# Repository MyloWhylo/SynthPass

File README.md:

# SynthPass

An open-source protocol & hardware design for to detect nose boops & transfer simple data, designed for protogen/synth fursuits.

Built to solve a very important problem. With SynthPass, you won't have to break character or pull off your paws and fumble with your phone to trade contact details. Just nose-boop, and SynthPass will automagically trade a small chunk of user-defined data, like a web link, username, or anything else that can fit in a couple hundred bytes of plain text. Then plug in your SynthPass at the end of the day and download all the data you've collected.

SynthPass is also designed to easily interface with nearly any protogen/synth fursuit. SynthPass hardware can be powered by a single 3.3V supply, and supports digital several digital interface options.

## Features

- ### Simple interface to fursuits
	- GPIO: pin HIGH (3.3V) when booped, LOW (0V) when not booped. Additional pin that's high
	- UART: Message for boop start/end
	- I2C: Register for boop status
    - Don't want to modify your firmware or connect the digital pins to your controller? The GPIO output can also drive an LED to indicate when another SynthPass is nearby and when a nose boop is detected.
- ### Advanced interface
	- UART/I2C Only
	- Approximate range & unique ID of peer prior to boop
	- Extra boop parameters (e.g. boop expression, color, name/species of peer)
- ### USB interface
    - Mass storage device for downloading collected data. Simply plug in the SynthPass into a computer and open `MESSAGES.HTM` in your web browser.
        - Edit the files `ME/BOOP.TXT` and `ME/PROX.TXT` to set your own messages to be transferred on proximity/boop
        - Edit `ME/SYNTHPAS.INI` to change settings for LED behavior, boop range, and enable proximity messages
    - Software bootloader switch for firmware updates over USB - send the character 'b' to the USB TTY that appears to switch to the USB bootloader.
## Hardware
SynthPass is based on the ultra-low-cost WCH CH57x series microcontrollers.
- ## 2.4GHz radio
	- Boop detection by RSSI (radio signal strength)
	- ISLER protocol for peer-to-peer and broadcast communication without need for pairing
	- CH572 also supports BLE (possibility for future companion app?)
- ## Protogen/Synth Suit Interface
	- 4-pin JST SH connector, compatible with QWIIC/Stemma QT (TODO?)
	- Single 3.3V input (possibly support 5V input with some hardware designs)
	- Option for I2C, UART, or GPIO communication protocol
	- Designed for easy integration with most synth/protogen heads

## Software
Using CH32Fun + iSLER library for communication

SynthPass communicates using BLE advertising frames with a fixed MAC address so that SynthPassdevices can easily be detected.

Communication (currently) uses a fixed channel (Channel 37) and PHY mode (1Mbps).

TODO document stuff better :3

## Development

**Building SynthPass**

SynthPass uses PlatformIO to manage the firmware toolchain, and the ch32fun framework to handle the ch572's hardware interfaces.

To compile the firmware, you'll need to:

- Clone the SynthPass repo `git clone https://github.com/JackToaster/SynthPass.git`
- Clone the ch33fun repo `git clone https://github.com/cnlohr/ch32fun.git`
- Run `pio run -e [board hardware target]`. `[board hardware target]` should be replaced with one of the targets defined in `platformio.ini`:
  - `nanoch57x` for the nanoch57x dev board
  - `pretzelslab` for the SynthPass hardware in this repo & the SynthPasses handed out at Anthrocon 2026
  - `axionqc` for AxionQc's hardware design

**Updating firmware**

We have a custom upload script built into the PlatformIO configuration for SynthPass, all you need to do to update the firmware is:

`pio run -e [board target] -t upload`

for the "official" Pretzel's Lab hardware: `pio run -e pretzelslab -t upload`

If the firmware is borked and the flashing script doesn't work, hold down the boot button while plugging in the SynthPass to force it into ISP bootloader mode.

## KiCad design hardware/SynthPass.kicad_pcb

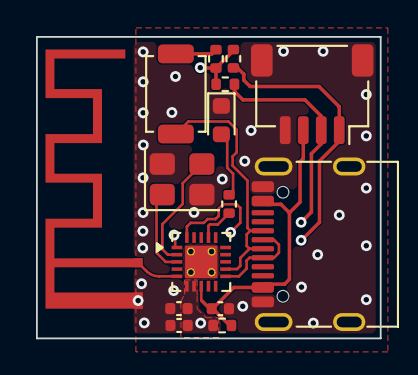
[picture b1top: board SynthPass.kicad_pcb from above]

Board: 4 copper layers, 19.1 x 16.8 mm, 15 parts (0 on the bottom side), 13 nets.

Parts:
AE1: SWRA117D; Texas_SWRA117D_2.4GHz_Right
C1, C3: 10u; C_0402_1005Metric
C4: 0.1u; C_0402_1005Metric
D1: LED_Small; LED_0603_1608Metric
J1: SM04B-SRSS-TB; JST_SH_SM04B-SRSS-TB_1x04-1MP_P1.00mm_Horizontal
J2: USB_C_Receptacle_USB2.0_16P; USB_C_Receptacle_G-Switch_GT-USB-7010ASV
R1, R5: 1K5; R_0402_1005Metric
R2, R3, R4: 5.1k; R_0402_1005Metric
SW1: SW_Push; SW_SPST_TS-1088-xR020
U1: CH572D; CH572D_New
Y1: 32MHz; Crystal_SMD_3225-4Pin_3.2x2.5mm

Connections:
+3V3: C3.1, C4.1, R1.2, R3.2, R4.2, R5.2, U1.6 (VDD33), U1.7 (VIO33)
/ANT: AE1.1 (FEED), U1.5 (ANT)
/XI: U1.3 (XI), Y1.1
/XO: U1.2 (XO), Y1.3
GND: AE1.2 (PCB_Trace), C1.2, C3.2, C4.2, D1.1 (K), J1.4, J1.MP (MountPin), J2.A1 (GND), J2.A12 (GND), J2.B1 (GND), J2.B12 (GND), J2.SH (SHIELD), U1.0 (GND), Y1.2, Y1.4
unnamed: D1.2 (A), R2.2
unnamed: R1.1, SW1.2
unnamed: R2.1, U1.17 (PA10)
SCL: J1.1, R3.1, U1.1 (SCL)
SDA: J1.2, R4.1, U1.20 (SDA)
UDN: J2.A7 (D-), J2.B7 (D-), U1.11 (UDM)
UDP: J2.A6 (D+), J2.B6 (D+), SW1.1, U1.12 (UDP)
VBUS: C1.1, J1.3, J2.A4 (VBUS), J2.A9 (VBUS), J2.B4 (VBUS), J2.B9 (VBUS), R5.1, U1.8 (V5)

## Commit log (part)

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2026-05-27 add preliminary (nfc) hardware
2026-05-27 Add USB bootloader flash script, jump to bootloader from app
2026-05-27 Implement MSC
2026-05-27 Flash-backed msc
2026-05-28 Message store cleanup and bugfixes
2026-05-28 work towards file handling on usb msc
2026-05-28 File storage change - single MD stream for messages + separate storage for attachment files
2026-05-28 Finalize hardware design, pending pinout confirmation
2026-05-28 Trimming for utf-8
2026-06-18 Create LICENSE
2026-06-18 Create hardware LICENSE
2026-06-18 Add boop
2026-06-19 Peer device state tracking and transmission queueing
2026-06-19 Create webusb flasher
2026-06-19 Radio bugfixes
2026-06-19 Add multiple board targets, LED/RSSI config
2026-06-29 Add config, fix USB MSC issues, boop transfers data
2026-06-29 Add message deletion path
